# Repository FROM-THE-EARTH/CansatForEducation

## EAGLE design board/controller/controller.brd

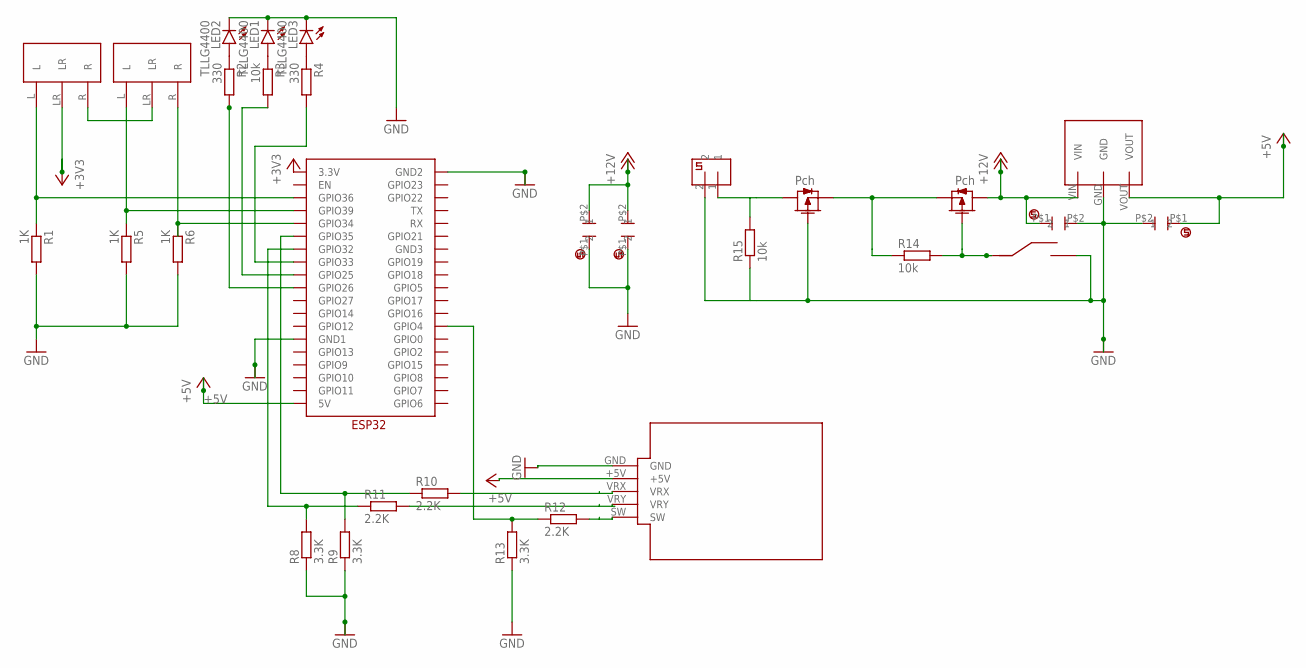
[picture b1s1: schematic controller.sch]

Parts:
CERAMIC_CAPACITOR1, CERAMIC_CAPACITOR2, CERAMIC_CAPACITOR3, CERAMIC_CAPACITOR4: CERAMIC_CAPACITOR
CONNECTOR2: 2PIN
JOY1: JOYSTICK_WITH_PINSOCKET; JOYSTICK
LED1, LED2, LED3: TLLG4400; LED3MM
R1, R5, R6: 1K; 0207/7
R2, R4: 330; 0207/7
R3, R14, R15: 10k; 0207/7
R8, R9, R13: 3.3K; 0207/7
R10, R11, R12: 2.2K; 0207/7
SRIDE_SWTCH1, SRIDE_SWTCH2: SRIDE_SWITCH
U$1, U$5: 2SJ681-PCH; 2SJ681
U$4: ESP32
U$6: M78AR05-1
U$8: SLIDESWITCH

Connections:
+3V3: SRIDE_SWTCH1.LR, U$4.3.3V
+5V: CERAMIC_CAPACITOR1.P$1 (1), JOY1.+5V, U$4.5V, U$6.VOUT
+12V: CERAMIC_CAPACITOR2.P$1 (1), CERAMIC_CAPACITOR3.P$2 (2), CERAMIC_CAPACITOR4.P$2 (2), U$5.DRAIN, U$6.VIN
GND: CERAMIC_CAPACITOR1.P$2 (2), CERAMIC_CAPACITOR2.P$2 (2), CERAMIC_CAPACITOR3.P$1 (1), CERAMIC_CAPACITOR4.P$1 (1), CONNECTOR2.2, JOY1.GND, LED1.K (C), LED2.K (C), LED3.K (C), R1.2, R5.2, R6.2, R8.1, R9.1, R13.1, R15.1, U$1.GATE, U$4.GND1, U$6.GND, U$8.C
unnamed: R14.1, U$1.SOURCE, U$5.SOURCE
unnamed: SRIDE_SWTCH1.R, SRIDE_SWTCH2.LR
unnamed: R14.2, U$5.GATE, U$8.A
unnamed: R1.1, SRIDE_SWTCH1.L, U$4.GPIO36
unnamed: CONNECTOR2.1, R15.2, U$1.DRAIN
unnamed: R5.1, SRIDE_SWTCH2.L, U$4.GPIO39
unnamed: R6.1, SRIDE_SWTCH2.R, U$4.GPIO34
unnamed: JOY1.VRX, R10.2
unnamed: R9.2, R10.1, U$4.GPIO35
unnamed: LED1.A, R3.1
unnamed: R12.1, R13.2, U$4.GPIO4
unnamed: LED2.A, R2.1
unnamed: LED3.A, R4.1
unnamed: R4.2, U$4.GPIO33
unnamed: R3.2, U$4.GPIO25
unnamed: R2.2, U$4.GPIO26
unnamed: JOY1.VRY, R11.2
unnamed: JOY1.SW, R12.2
SCL: R8.2, R11.1, U$4.GPIO32

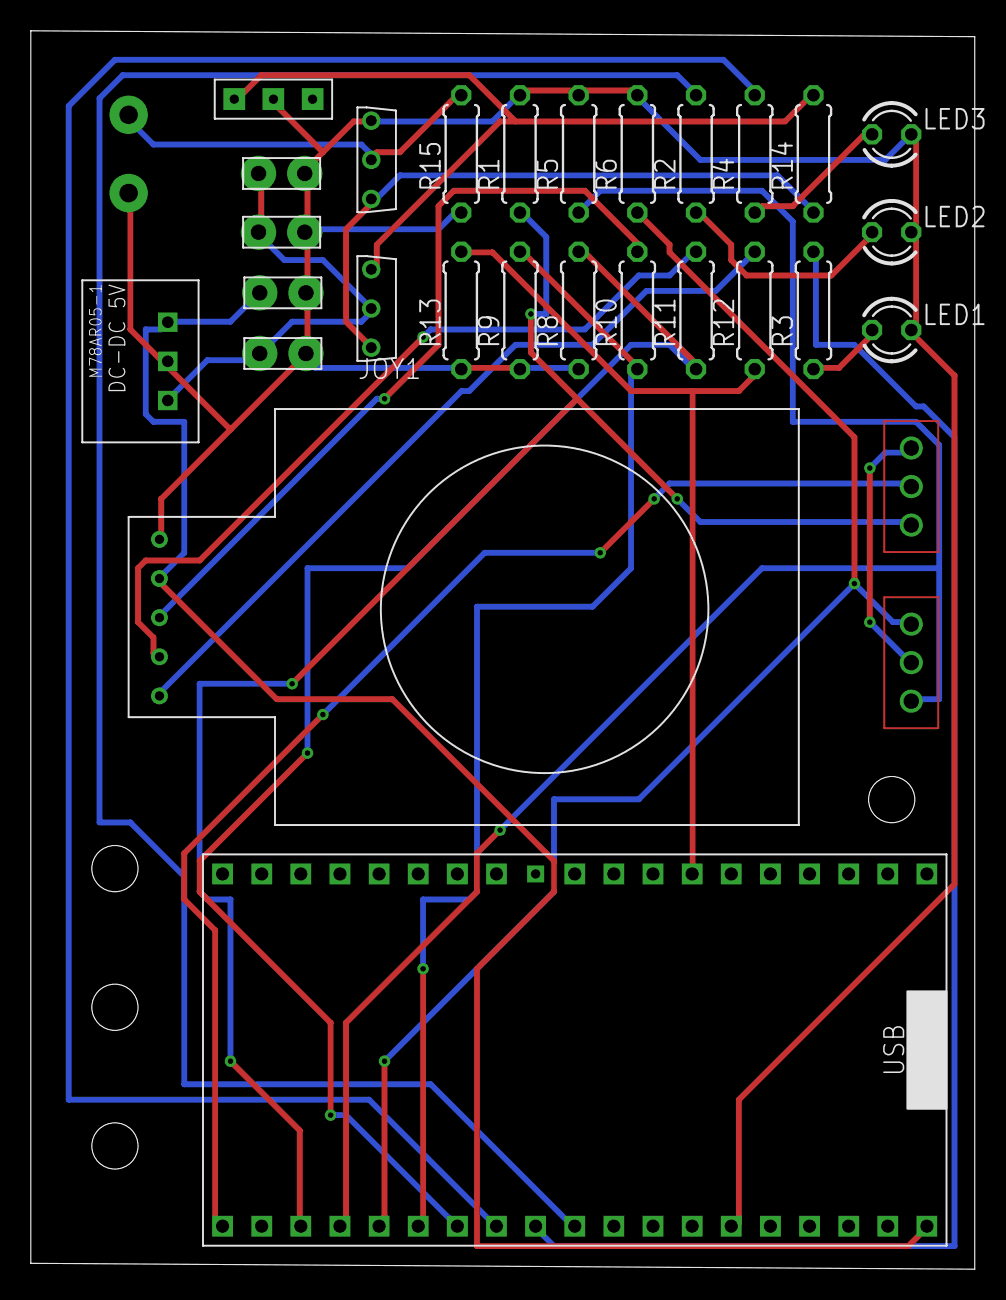
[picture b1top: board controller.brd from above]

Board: 2 copper layers, 61.3 x 80.4 mm, 30 parts (0 on the bottom side), 23 nets.

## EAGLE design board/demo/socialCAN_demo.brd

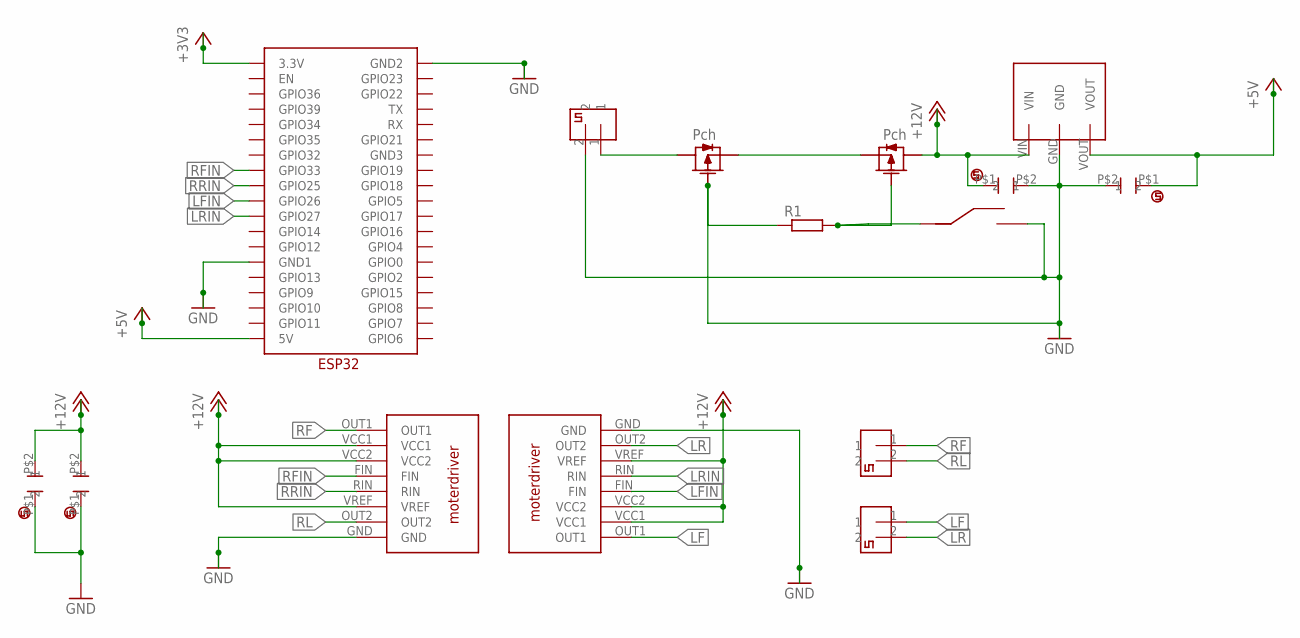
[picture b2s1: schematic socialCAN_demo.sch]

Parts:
CERAMIC_CAPACITOR1, CERAMIC_CAPACITOR2, CERAMIC_CAPACITOR3, CERAMIC_CAPACITOR4: CERAMIC_CAPACITOR
CONNECTOR1, CONNECTOR2, CONNECTOR3: 2PIN
R1: R-EU_0207/10; 0207/10
U$1, U$5: 2SJ681-PCH; 2SJ681
U$4: ESP32
U$6: M78AR05-1
U$8: SLIDESWITCH
U$15, U$16: MOTORDRIVER

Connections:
+3V3: U$4.3.3V
+5V: CERAMIC_CAPACITOR1.P$1 (1), U$4.5V, U$6.VOUT
+12V: CERAMIC_CAPACITOR2.P$1 (1), CERAMIC_CAPACITOR3.P$2 (2), CERAMIC_CAPACITOR4.P$2 (2), U$5.DRAIN, U$6.VIN, U$15.VCC1, U$15.VCC2, U$15.VREF, U$16.VCC1, U$16.VCC2, U$16.VREF
GND: CERAMIC_CAPACITOR1.P$2 (2), CERAMIC_CAPACITOR2.P$2 (2), CERAMIC_CAPACITOR3.P$1 (1), CERAMIC_CAPACITOR4.P$1 (1), CONNECTOR2.2, R1.1, U$1.GATE, U$4.GND1, U$6.GND, U$8.C, U$15.GND, U$16.GND
LF: CONNECTOR3.1, U$16.OUT1
LFIN: U$4.GPIO26, U$16.FIN
LR: CONNECTOR3.2, U$16.OUT2
LRIN: U$4.GPIO27, U$16.RIN
unnamed: U$1.SOURCE, U$5.SOURCE
unnamed: R1.2, U$5.GATE, U$8.A
unnamed: CONNECTOR2.1, U$1.DRAIN
RF: CONNECTOR1.1, U$15.OUT1
RFIN: U$4.GPIO33, U$15.FIN
RL: CONNECTOR1.2, U$15.OUT2
RRIN: U$4.GPIO25, U$15.RIN

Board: 2 copper layers, 15 parts (0 on the bottom side), 14 nets, no tracks yet.

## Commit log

2024-03-13 基板を追加
2024-03-13 基板データを追加
